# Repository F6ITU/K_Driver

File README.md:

# K_Driver
Ajax Telamon, 10 to 30 dBm driver to feed LDMOS RF amplifier

Ajax is a cascade of four OPA2674 op-amps, designed to amplify the signal from a DAC by around 20/25 dB (between 0 to 5 dBm of input power 27 dBm out). 

The comfort zone of this amplifier is around half a watt of power.

The origin of the diagram is lost in the mists of time.

It can be found in the archives of the OpenHPSDR Penelope and Pennylane project, a 1/2 watt exciter (https://openhpsdr.org/wiki/index.php?title=PENELOPE) 
(following a AD9744ARU DAC).

It is also used in the 14HAM-DK2, an impressive project by F4JGL.  (https://sites.google.com/view/projet-14ham-dk2/les-%C3%A9l%C3%A9ments-du-projet/modules-ampli-hf-%C3%A9mission/module-driver). 

It is used to directly attack a push-pull made of MRF101AN/BN , in other words Kjell LA2NI's OpenHPSDR "MUNIN 100" amplifier (https://github.com/F6ITU/K_Munin100_Fork)

This umpteenth version has no other ambition than to provide exactly the same "service," but in a smaller size, with the PCB measuring only 6.5 x 2.5 cm.

The shielding of the assembly is left to the discretion of each user.

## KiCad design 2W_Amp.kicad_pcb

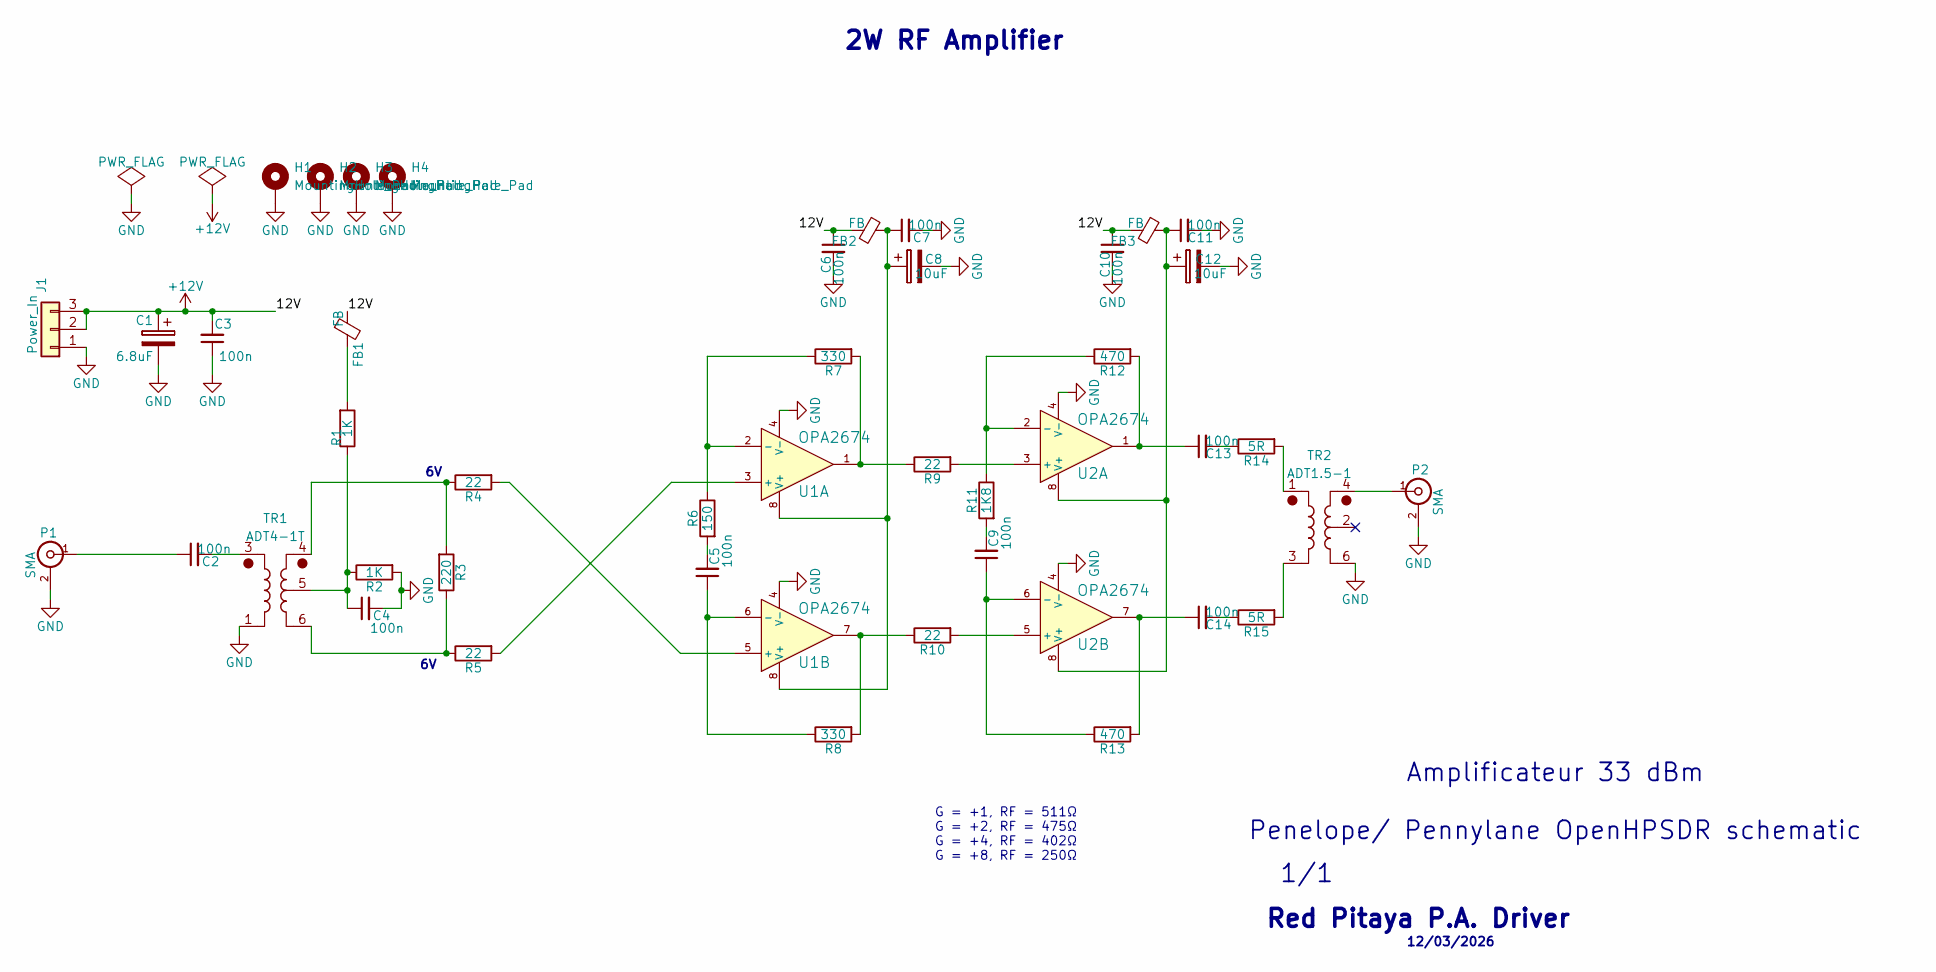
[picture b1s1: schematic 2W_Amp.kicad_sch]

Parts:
C1: 6.8uF; CP_EIA-6032-28_Kemet-C_HandSolder
C2, C3, C4, C5, C6, C7, C9, C10, C11, C13, C14: 100n; C_0805_2012Metric_Pad1.18x1.45mm_HandSolder
C8, C12: 10uF; CP_EIA-6032-28_Kemet-C_HandSolder
FB1, FB2, FB3: FB; R_0805_2012Metric_Pad1.20x1.40mm_HandSolder
H1, H2, H3, H4: MountingHole_Pad; MountingHole_3.2mm_M3_DIN965_Pad_TopBottom
J1: Power_In; Molex_KK-254_AE-6410-03A_1x03_P2.54mm_Vertical
P1, P2: SMA; SMA_PINS
R1, R2: 1K; R_0805_2012Metric_Pad1.20x1.40mm_HandSolder
R3: 220; R_0805_2012Metric_Pad1.20x1.40mm_HandSolder
R4, R5, R9, R10: 22; R_0805_2012Metric_Pad1.20x1.40mm_HandSolder
R6: 150; R_0805_2012Metric_Pad1.20x1.40mm_HandSolder
R7, R8: 330; R_0805_2012Metric_Pad1.20x1.40mm_HandSolder
R11: 1K8; R_0805_2012Metric_Pad1.20x1.40mm_HandSolder
R12, R13: 470; R_0805_2012Metric_Pad1.20x1.40mm_HandSolder
R14, R15: 5R; R_0805_2012Metric_Pad1.20x1.40mm_HandSolder
TR1: ADT4-1T; Mini-Circuits_CD542_H2.84mm
TR2: ADT1.5-1; Mini-Circuits_CD542_H2.84mm
U1, U2: OPA2674; SOIC-8_3.9x4.9mm_P1.27mm

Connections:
+12V: C1.1, C3.2, C6.1, C10.1, FB1.1, FB2.2, FB3.2, J1.2, J1.3
GND: C1.2, C3.1, C4.2, C6.2, C7.2, C8.2, C10.2, C11.2, C12.2, H1.1, H2.1, H3.1, H4.1, J1.1, P1.2 (Ext), P2.2 (Ext), R2.2, TR1.1, TR2.6, U1.4 (V-), U2.4 (V-)
unnamed: C2.2, TR1.3
unnamed: C4.1, R1.1, R2.1, TR1.5
unnamed: C5.2, R6.2
unnamed: C9.2, R11.2
unnamed: C13.1, R12.2, U2.1
unnamed: C13.2, R14.1
unnamed: C14.1, R13.2, U2.7
unnamed: C14.2, R15.1
unnamed: FB1.2, R1.2
unnamed: C2.1, P1.1 (In)
unnamed: P2.1 (In), TR2.4
unnamed: R3.1, R5.1, TR1.6
unnamed: R3.2, R4.1, TR1.4
unnamed: R7.2, R9.1, U1.1
unnamed: R8.2, R10.1, U1.7
unnamed: R14.2, TR2.1
unnamed: R15.2, TR2.3
unnamed: R5.2, U1.3 (+)
unnamed: R6.1, R7.1, U1.2 (-)
unnamed: C7.1, C8.1, FB2.1, U1.8 (V+)
unnamed: R4.2, U1.5 (+)
unnamed: C5.1, R8.1, U1.6 (-)
unnamed: R9.2, U2.3 (+)
unnamed: R11.1, R12.1, U2.2 (-)
unnamed: C11.1, C12.1, FB3.1, U2.8 (V+)
unnamed: R10.2, U2.5 (+)
unnamed: C9.1, R13.1, U2.6 (-)

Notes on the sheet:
1/1
Amplificateur 33 dBm Penelope/ Pennylane OpenHPSDR schematic
2W RF Amplifier
G = +1, RF = 511Ω G = +2, RF = 475Ω G = +4, RF = 402Ω G = +8, RF = 250Ω
12/03/2026
Red Pitaya P.A. Driver

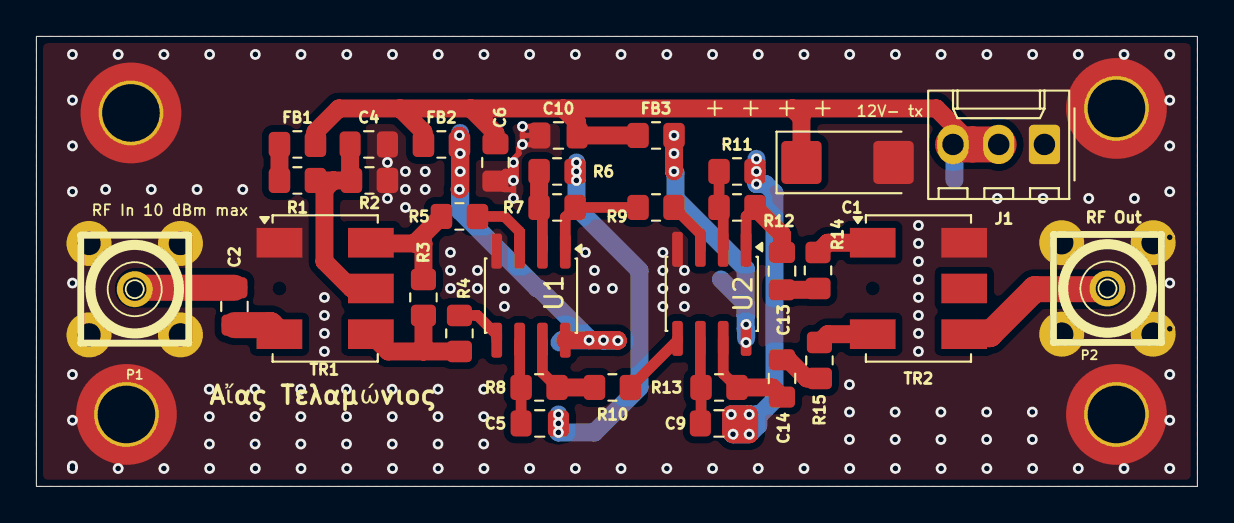
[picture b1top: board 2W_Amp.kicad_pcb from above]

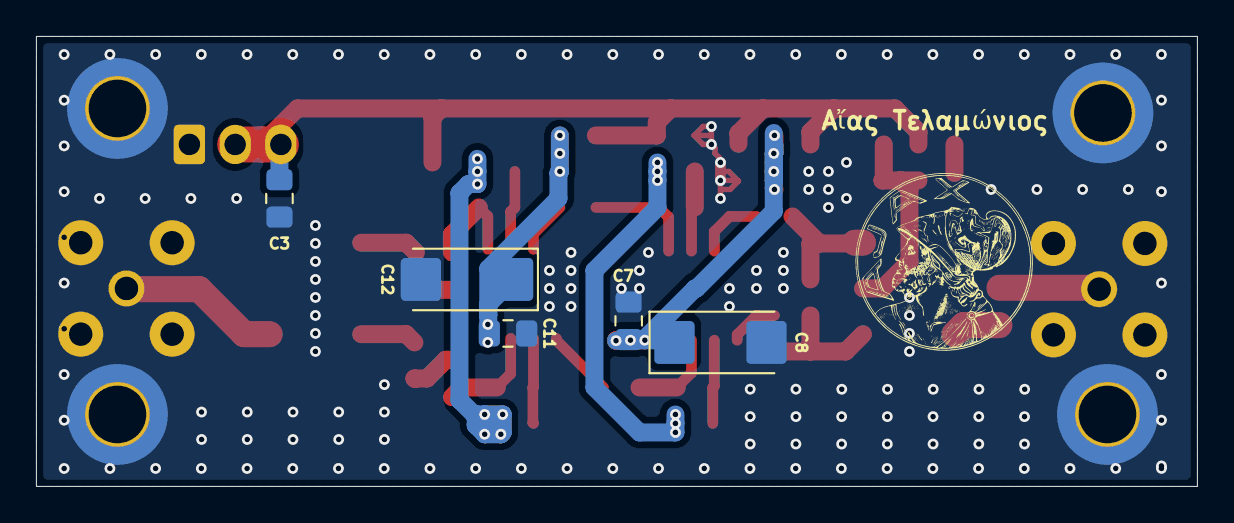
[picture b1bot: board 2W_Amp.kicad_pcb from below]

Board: 2 copper layers, 64.5 x 25.0 mm, 43 parts (5 on the bottom side), 29 nets.

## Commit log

2026-03-13 first commit with gerber and iBom
2026-03-13 readme picture added
2026-03-13 some cleanup later...
2026-03-13 yet some other small adjustments
2026-03-13 yet some other other small adjustments
2026-03-14 decoupling on lower side, documentation added
2026-03-23 kicad 10 update
2026-04-01 picture and schematic pdf file added
2026-05-16 minor cosmetic changes
